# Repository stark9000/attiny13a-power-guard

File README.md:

# ATtiny13A Power Guard

A mains under/over-voltage cutoff with a start delay, built around an ATtiny13A. It keeps the load switched off until mains has been stable for a set time, and drops it again if the voltage leaves the safe band.

Inspired by the Scorpionz 12F683 Power Guard (https://scopionz.blogspot.com/2015/09/simple-power-guard-using-12f683.html). The firmware here is a fresh implementation.

> **⚠️ Not tested.** The firmware, circuit and calculations in this repo have not been tested on real hardware. Treat everything as a starting point, verify it yourself, and calibrate before trusting it with any load.

> **⚠️ Mains voltage is dangerous.** Use a fuse, a varistor (MOV), proper insulation, a suitable enclosure and correct mains clearances. Work from an isolation transformer where possible. You build and use this at your own risk.

## Features

- Relay is **off at power-up**; a green LED blinks while the guard waits
- Relay switches on only after mains has stayed in the good band for **30 s** (configurable `DELAY_S`)
- Trips if mains stays out of band for **200 ms**
- **Hysteresis** to avoid chattering at the edges
- Yellow LED = low voltage, red LED = high voltage
- 500 ms watchdog; after any reset or blackout the full start delay runs again
- Tiny footprint: about 350 bytes of flash, no timers or interrupts, 8-bit ADC only

## Thresholds (230 V mains example)

| | Low side | High side |
|---|---|---|
| Trip (relay drops) | below 200 V | above 260 V |
| Good again (countdown runs) | above 210 V | below 250 V |

## Pin map

| Pin | Function |
|---|---|
| PB0 | Relay driver |
| PB1 | Green LED (blink = waiting, solid = load on) |
| PB2 | Voltage sense (ADC1, filtered DC) |
| PB3 | Yellow LED (low voltage) |
| PB4 | Red LED (high voltage) |
| PB5 | RESET (left free for ISP programming) |

## How it works

Mains goes through a fuse into a small centre-tapped transformer (9-0-9 V in the reference circuit), a two-diode full-wave rectifier and a bulk capacitor. That DC rail feeds three things:

- a 5 V regulator (7805) that powers the ATtiny13A and also acts as the ADC reference
- a resistor divider plus 10 µF filter capacitor that goes to PB2 for voltage sensing
- the relay coil, switched by an NPN transistor from PB0

The firmware reads the sense voltage every 20 ms using the left-adjusted 8-bit ADC result and compares it with limits calculated from a single calibration constant `K` (ADC counts per mains volt × 1000). Two states are used: RUN (load on, checks the trip limits) and WAIT (load off, checks the stricter restore limits and counts down the start delay).

The full tutorial document covers the circuit, component values, transformer selection, threshold maths, relay voltage dip compensation, fuses and troubleshooting.

## Versions

- **v1**: first version, assumes a 12 V transformer and a 7805 supply, fixed scaling for 8-bit ADC counts.
- **v2**: updated for the 9-0-9 V centre-tapped transformer circuit, adds the `K` calibration constant and `DIP` relay-dip compensation (`DIP` defaults to 0, meaning no compensation).

Each version has an Arduino IDE sketch (`.ino`) and a plain AVR C version (`.c`).

## Build and upload (Arduino IDE)

1. In **File → Preferences → Additional Boards Manager URLs**, add:
   `https://mcudude.github.io/MicroCore/package_MCUdude_MicroCore_index.json`
2. **Boards Manager**: install **MicroCore**
3. **Tools**: Board = ATtiny13, Clock = 1.2 MHz internal, BOD = 4.3 V
4. **Tools → Burn Bootloader** once (with an ISP programmer this only writes the fuses)
5. **Sketch → Upload Using Programmer**

### Fuses

| Fuse | Value | Meaning |
|---|---|---|
| Low | `0x6A` | 9.6 MHz internal RC divided by 8 = 1.2 MHz, SPI programming on (use `0x7A` for 9.6 MHz) |
| High | `0xF9` | Brown-out detector at 4.3 V, reset pin kept, debugWIRE off |

Example with avrdude (adjust the programmer to yours):

```
avrdude -c usbasp -p t13 -U lfuse:w:0x6A:m -U hfuse:w:0xF9:m
```

**Never program RSTDISBL (high fuse `0xF8`).** It turns PB5 into a normal pin and you would then need a high-voltage programmer to recover the chip. Always check the fuse bytes against a fuse calculator and the datasheet before burning.

## Calibration

Calibrate once per finished board, using the real regulator and divider.

1. With normal mains and the relay on, measure the real mains voltage, the voltage at PB2 and the 5 V rail at the MCU.
2. Compute `K = 256 × Vpin / (Vcc × Vmains) × 1000` and set it in the sketch (default 640).
3. Measure the relay dip (reading with relay off vs on) and set `DIP` in per-mille (35 = 3.5 %).
4. Verify by temporarily moving a threshold close to the present mains voltage and checking that the LEDs and relay behave as expected.
5. If you have a variac, confirm the real trip points at 200 V and 260 V.

## Safety notes

- The guard reacts in about 200 ms. It protects against sags, surges and bad restores, but cannot clip fast spikes, which is what the MOV is for.
- Choose relay contacts rated for the load type (motors and compressors need a higher rating).
- Check the relay coil voltage at the highest mains you expect.

## License

MIT

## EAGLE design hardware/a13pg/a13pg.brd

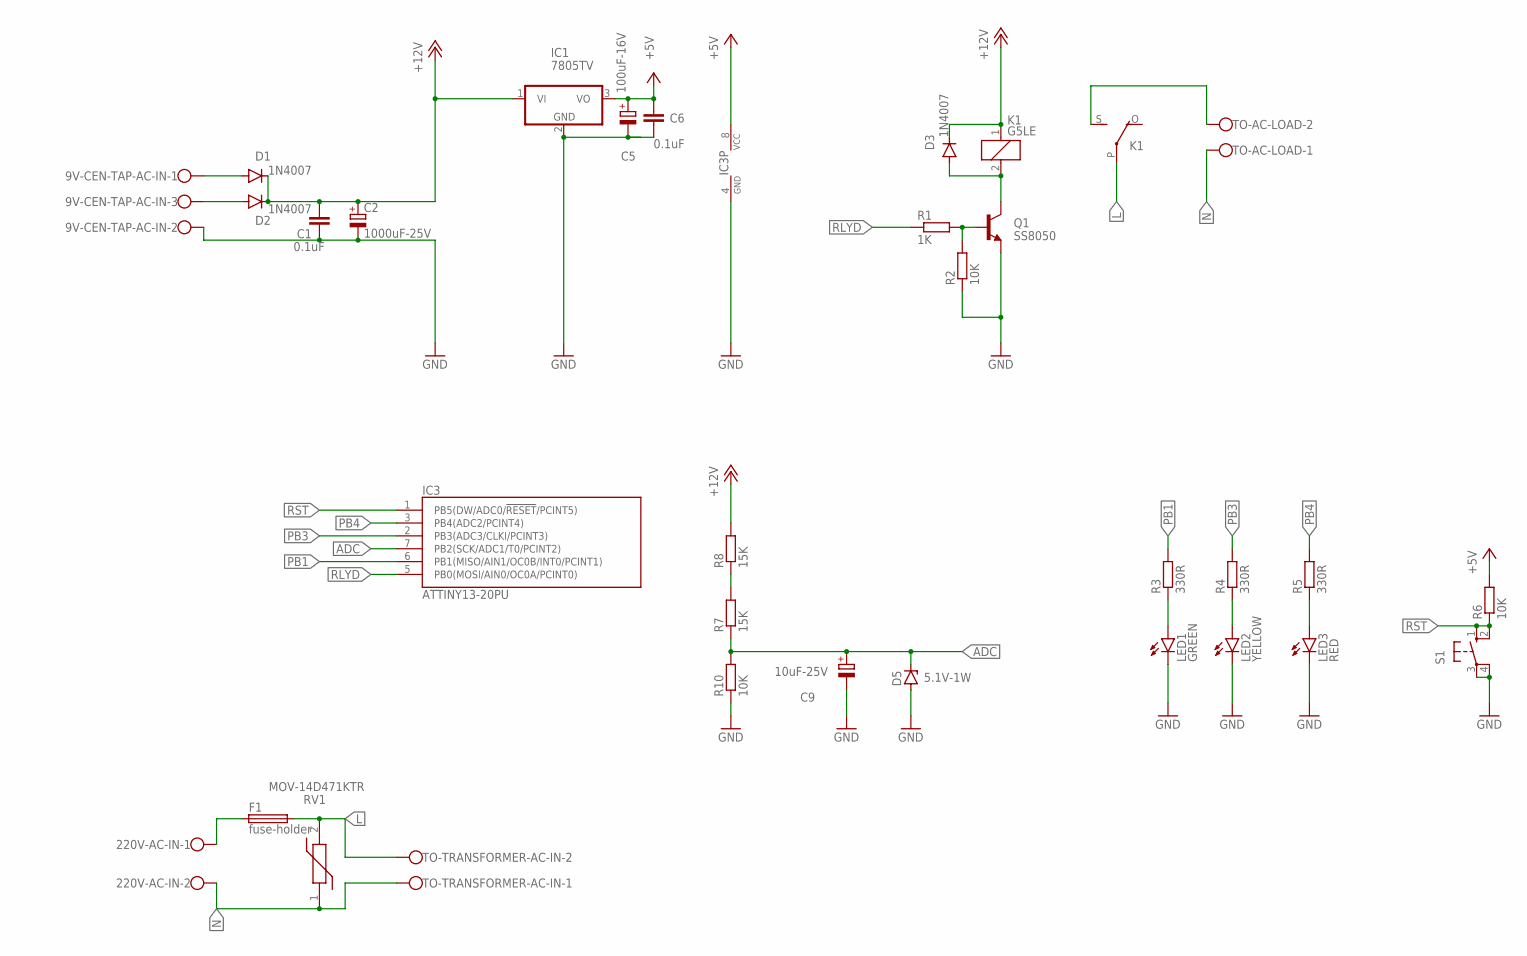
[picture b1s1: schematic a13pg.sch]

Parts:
9V-CEN-TAP-AC-IN: W237-103
220V-AC-IN: 2pinsctg; W237-102
C1, C6: 0.1uF; C075-032X103
C2: 1000uF-25V; E5-8,5
C5: 100uF-16V; E2,5-6E
C9: 10uF-25V; E2,5-6E
D1, D2, D3: 1N4007; DO41-10
D5: 5.1V-1W; DO35Z10
F1: fuse-holder; SH22
IC1: 7805TV; TO220V
IC3: ATTINY13-20PU; DIL08
K1: G5LE
LED1: GREEN; LED5MM
LED2: YELLOW; LED5MM
LED3: RED; LED5MM
Q1: SS8050; TO92
R1: 1K; 0207/7
R2, R6, R10: 10K; 0207/7
R3, R4, R5: 330R; 0207/7
R7, R8: 15K; 0207/7
RV1: MOV-14D471KTR; MOV14D471K
S1: pbtn4pin; B3F-10XX
TO-AC-LOAD: W237-102
TO-TRANSFORMER-AC-IN: W237-102

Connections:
+5V: C5.+, C6.2, IC1.3 (VO), IC3.8 (VCC), R6.2
+12V: C1.2, C2.+, D1.C, D2.C, D3.C, IC1.1 (VI), K1.1, R8.2
ADC: C9.+, D5.C, IC3.7 (PB2(SCK/ADC1/T0/PCINT2)), R7.1, R10.2
GND: 9V-CEN-TAP-AC-IN.2, C1.1, C2.-, C5.-, C6.1, C9.-, D5.A, IC1.2 (GND), IC3.4 (GND), LED1.K (C), LED2.K (C), LED3.K (C), Q1.3 (E), R2.1, R10.1, S1.3, S1.4 (P1)
L: F1.2, K1.P, RV1.2, TO-TRANSFORMER-AC-IN.2
N: 220V-AC-IN.2, RV1.1, TO-AC-LOAD.1, TO-TRANSFORMER-AC-IN.1
unnamed: R7.2, R8.1
unnamed: 9V-CEN-TAP-AC-IN.1, D1.A
unnamed: 9V-CEN-TAP-AC-IN.3, D2.A
unnamed: K1.S, TO-AC-LOAD.2
unnamed: D3.A, K1.2, Q1.1 (C)
unnamed: Q1.2 (B), R1.2, R2.2
unnamed: LED1.A, R3.1
unnamed: LED2.A, R4.1
unnamed: LED3.A, R5.1
unnamed: 220V-AC-IN.1, F1.1
PB1: IC3.6 (PB1(MISO/AIN1/OC0B/INT0/PCINT1)), R3.2
PB3: IC3.2 (PB3(ADC3/CLKI/PCINT3)), R4.2
PB4: IC3.3 (PB4(ADC2/PCINT4)), R5.2
RLYD: IC3.5 (PB0(MOSI/AIN0/OC0A/PCINT0)), R1.1
RST: IC3.1 (PB5(DW/ADC0/!RESET!/PCINT5)), R6.1, S1.1 (S), S1.2 (S1)

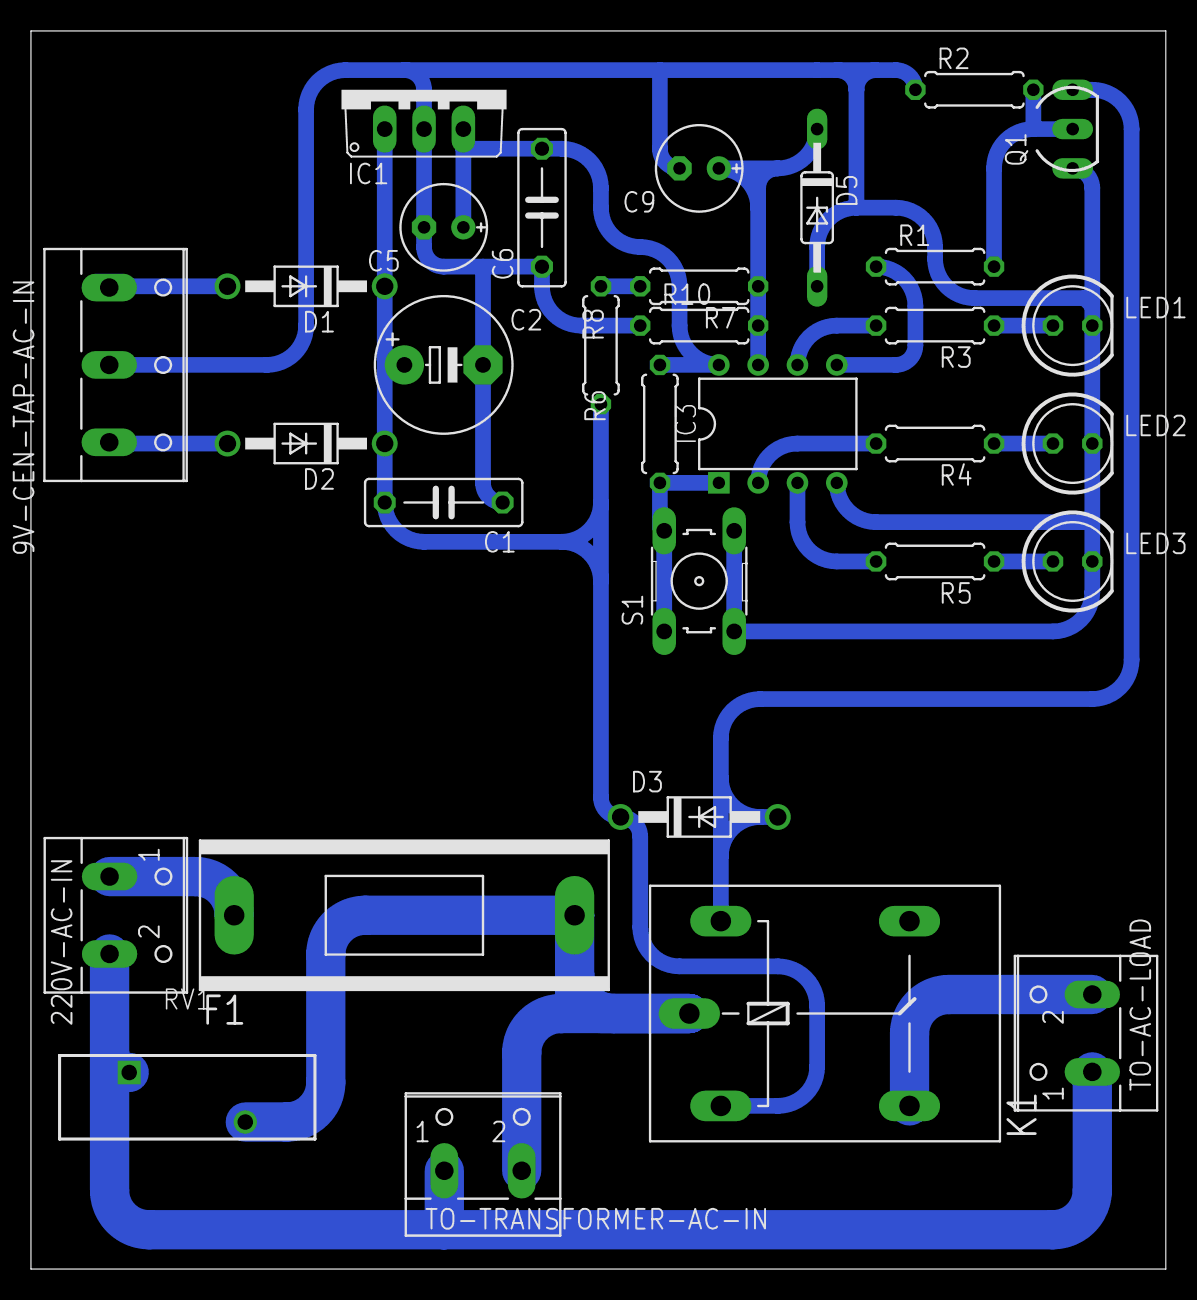
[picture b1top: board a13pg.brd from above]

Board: 2 copper layers, 73.3 x 80.0 mm, 32 parts (0 on the bottom side), 21 nets.

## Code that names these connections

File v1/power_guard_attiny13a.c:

/*
 * Power Guard - ATtiny13A
 * -----------------------------------------------------------------------
 * Disconnects the load when mains voltage is too low or too high, and
 * reconnects it only after the voltage has stayed good for START_DELAY_S.
 *
 * Hardware assumptions
 *   - 12 V transformer -> rectifier -> filter cap -> divider -> PB2.
 *     The sense voltage must be smoothed DC (about 3 V at 240 V mains).
 *   - MCU powered from a regulated 5 V (7805); VCC is the ADC reference.
 *   - Active-high outputs. Put a ~10k pull-down on the relay driver base/gate
 *     so the relay stays off while the MCU is in reset.
 *
 * Pins
 *   PB0  relay driver        PB1  green LED (blink = waiting, solid = on)
 *   PB2  voltage sense (ADC1)  PB3  yellow LED (low voltage)
 *   PB4  red LED (high voltage) PB5  RESET (left free for ISP)
 *
 * Fuses (factory default clock: 9.6 MHz RC / 8 = 1.2 MHz)
 *   Set the brown-out detector to 4.3 V so the chip resets (relay off)
 *   when the 5 V rail sags. Verify the exact fuse bytes with a fuse
 *   calculator for your programmer before burning.
 *
 * Calibration
 *   Thresholds are in volts of mains and converted at compile time using
 *   ADC_PER_VOLT_X10000. Default 25575 matches the original design:
 *       ADC = V * 12 * 1023 / (240 * 5 * 4)
 *   Trim the constant per board if your divider/transformer differ.
 *
 * Build:  avr-gcc -mmcu=attiny13a -Os -o pg.elf power_guard_attiny13a.c
 *         avr-objcopy -O ihex -R .eeprom pg.elf pg.hex
 * -----------------------------------------------------------------------
 */

#ifndef F_CPU
#define F_CPU 1200000UL
#endif

#include <avr/io.h>
#include <avr/interrupt.h>
#include <avr/wdt.h>
#include <stdint.h>

/* ---------------- user settings ---------------- */
#define START_DELAY_S        30      /* good voltage needed this long (max 650) */
#define V_LOW_TRIP           200     /* cut off below this (V)                  */
#define V_LOW_RESTORE        210     /* must rise above this to be "good" (V)   */
#define V_HIGH_RESTORE       250     /* must fall below this to be "good" (V)   */
#define V_HIGH_TRIP          260     /* cut off above this (V)                  */
#define TRIP_DEBOUNCE_MS     200     /* out-of-band this long before trip (max 2550) */
#define ADC_PER_VOLT_X10000  25575UL
/* ------------------------------------------------ */

#if !(V_LOW_TRIP < V_LOW_RESTORE && V_LOW_RESTORE < V_HIGH_RESTORE && V_HIGH_RESTORE < V_HIGH_TRIP)
#error "Thresholds must satisfy LOW_TRIP < LOW_RESTORE < HIGH_RESTORE < HIGH_TRIP"
#endif
#if START_DELAY_S > 650
#error "START_DELAY_S too large"
#endif
#if TRIP_DEBOUNCE_MS > 2550
#error "TRIP_DEBOUNCE_MS too large"
#endif

#define V2ADC(v) ((uint16_t)(((uint32_t)(v) * ADC_PER_VOLT_X10000) / 10000UL))

#define ADC_LOW_TRIP     V2ADC(V_LOW_TRIP)
#define ADC_LOW_RESTORE  V2ADC(V_LOW_RESTORE)
#define ADC_HIGH_RESTORE V2ADC(V_HIGH_RESTORE)
#define ADC_HIGH_TRIP    V2ADC(V_HIGH_TRIP)

#define TICKS_PER_SEC    100U                         /* 10 ms tick */
#define START_DELAY_TICKS ((uint16_t)(START_DELAY_S * TICKS_PER_SEC))
#define TRIP_TICKS       ((uint8_t)(TRIP_DEBOUNCE_MS / 10))
#define BLINK_TICKS      50U                          /* 500 ms toggle */

#define PIN_RELAY PB0
#define PIN_GREEN PB1
#define PIN_YELLOW PB3
#define PIN_RED   PB4

/* ADC clock should be 50..200 kHz; Timer0 gives a ~100 Hz tick */
#if F_CPU == 1200000UL
  #define ADC_PRESCALE ((1 << ADPS1) | (1 << ADPS0))          /* /8  -> 150 kHz */
  #define T0_PRESCALE  ((1 << CS01) | (1 << CS00))            /* /64            */
  #define T0_TOP       187                                    /* ~99.7 Hz       */
#elif F_CPU == 9600000UL
  #define ADC_PRESCALE ((1 << ADPS2) | (1 << ADPS1))          /* /64 -> 150 kHz */
  #define T0_PRESCALE  ((1 << CS02) | (1 << CS00))            /* /1024          */
  #define T0_TOP       93                                     /* ~99.7 Hz       */
#else
  #error "Unsupported F_CPU: use 1.2 MHz or 9.6 MHz"
#endif

enum { ST_WAIT, ST_RUN };

static volatile uint8_t tick;

ISR(TIM0_COMPA_vect)
{
    tick = 1;
}

static uint16_t adc_read(void)
{
    ADCSRA |= (1 << ADSC);
    while (ADCSRA & (1 << ADSC))
        ;
    return ADC;
}

int main(void)
{
    uint8_t  state = ST_WAIT;
    uint8_t  bad = 0;
    uint8_t  blink = 0;
    uint16_t remaining = START_DELAY_TICKS;
    uint16_t acc = 0;
    uint16_t v, i;

    wdt_reset();
    MCUSR = 0;
    wdt_enable(WDTO_500MS);

    /* outputs: relay and LEDs, all off at start */
    DDRB  = (1 << PIN_RELAY) | (1 << PIN_GREEN) | (1 << PIN_YELLOW) | (1 << PIN_RED);
    PORTB = 0;

    /* ADC: VCC reference, ADC1 (PB2), right-adjusted */
    ADMUX  = (1 << MUX0);
    DIDR0  = (1 << ADC1D);
    ADCSRA = (1 << ADEN) | ADC_PRESCALE;
    (void)adc_read();                       /* discard first conversion */
    for (i = 0; i < 8; i++)                 /* prefill the filter */
        acc += adc_read();

    /* Timer0: CTC, 10 ms tick */
    TCCR0A = (1 << WGM01);
    OCR0A  = T0_TOP;
    TIMSK0 = (1 << OCIE0A);
    TCCR0B = T0_PRESCALE;
    sei();

    for (;;) {
        while (!tick)
            ;
        tick = 0;
        wdt_reset();

        /* smoothed reading: IIR filter, time constant ~80 ms */
        acc = acc - (acc >> 3) + adc_read();
        v = acc >> 3;

        if (state == ST_RUN) {
            if (v < ADC_LOW_TRIP || v > ADC_HIGH_TRIP) {
                if (++bad >= TRIP_TICKS) {
                    PORTB &= ~((1 << PIN_RELAY) | (1 << PIN_GREEN));   /* load off */
                    remaining = START_DELAY_TICKS;
                    blink = 0;
                    state = ST_WAIT;
                }
            } else {
                bad = 0;
            }
        } else { /* ST_WAIT */
            uint8_t low  = (v < ADC_LOW_RESTORE);
            uint8_t high = (v > ADC_HIGH_RESTORE);
            uint8_t good = !(low || high);

            /* one fault LED at a time */
            if (low)       { PORTB |=  (1 << PIN_YELLOW); PORTB &= ~(1 << PIN_RED);    }
            else if (high) { PORTB |=  (1 << PIN_RED);    PORTB &= ~(1 << PIN_YELLOW); }
            else           { PORTB &= ~((1 << PIN_YELLOW) | (1 << PIN_RED)); }

            if (!good)           remaining = START_DELAY_TICKS;  /* restart countdown */
            else if (remaining)  remaining--;

            if (++blink >= BLINK_TICKS) {
                blink = 0;
                PORTB ^= (1 << PIN_GREEN);
            }

            if (good && remaining == 0) {
                PORTB |= (1 << PIN_RELAY) | (1 << PIN_GREEN);    /* load on */
                bad = 0;
                state = ST_RUN;
            }
        }
    }
}
